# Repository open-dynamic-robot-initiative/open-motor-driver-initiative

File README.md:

# Software for the Open Motor Driver Initiative project - uOmodri board

## Required installs
In order to use the UOMODRI projects, you must install [Code Composer Studio (CCS)](https://software-dl.ti.com/ccs/esd/documents/ccs_downloads.html) and [C2000Ware library](https://www.ti.com/tool/C2000WARE#downloads) from Texas Instruments. C2000Ware Motor Control SDK is not necessary anymore. 
The [installation](https://software-dl.ti.com/ccs/esd/documents/users_guide/index_installation.html) procedure is available on TI website.
For Linux users, don't forget to install USB drivers (everything is explained on Texas Instrument website).
When installing CCS, prefer a custom installation and check "C2000 real-time MCUs" installation.

## Repository description
This repository contains one project:
	**uOmodri_c28** : Main project. Implements current, speed and position control for PMSM along with a SPI communication for commands or debug. 
3 Files are mainly used for configuration:
- inc\uomodri_user_defines.h : Saves all the defines used in the project.
- inc\uomodri_hal_config_handlers.h : Structures necessaries during initialization phase.
- inc\uomodri_prj_config_handlers.h : Structures used in the running phase of the project.

## How to import these project
After cloning the repository, you can import the projects by doing Project > Import CCS project.
The last thing you must do before being able to compile the projects is to define the path to your C2000Ware library.
To do so, right click on the  project, and then Properties > Resource > Linked Resources.
Now modify the C2000WARE_ROOT path to match your own C2000Ware library folder path.
The folder should be named something like "C2000Ware_4_01_00_00" for the 4.01.00.00 version.
Verify that PARENT_LOC and WORKSPACE_LOC point on your own working workspace.

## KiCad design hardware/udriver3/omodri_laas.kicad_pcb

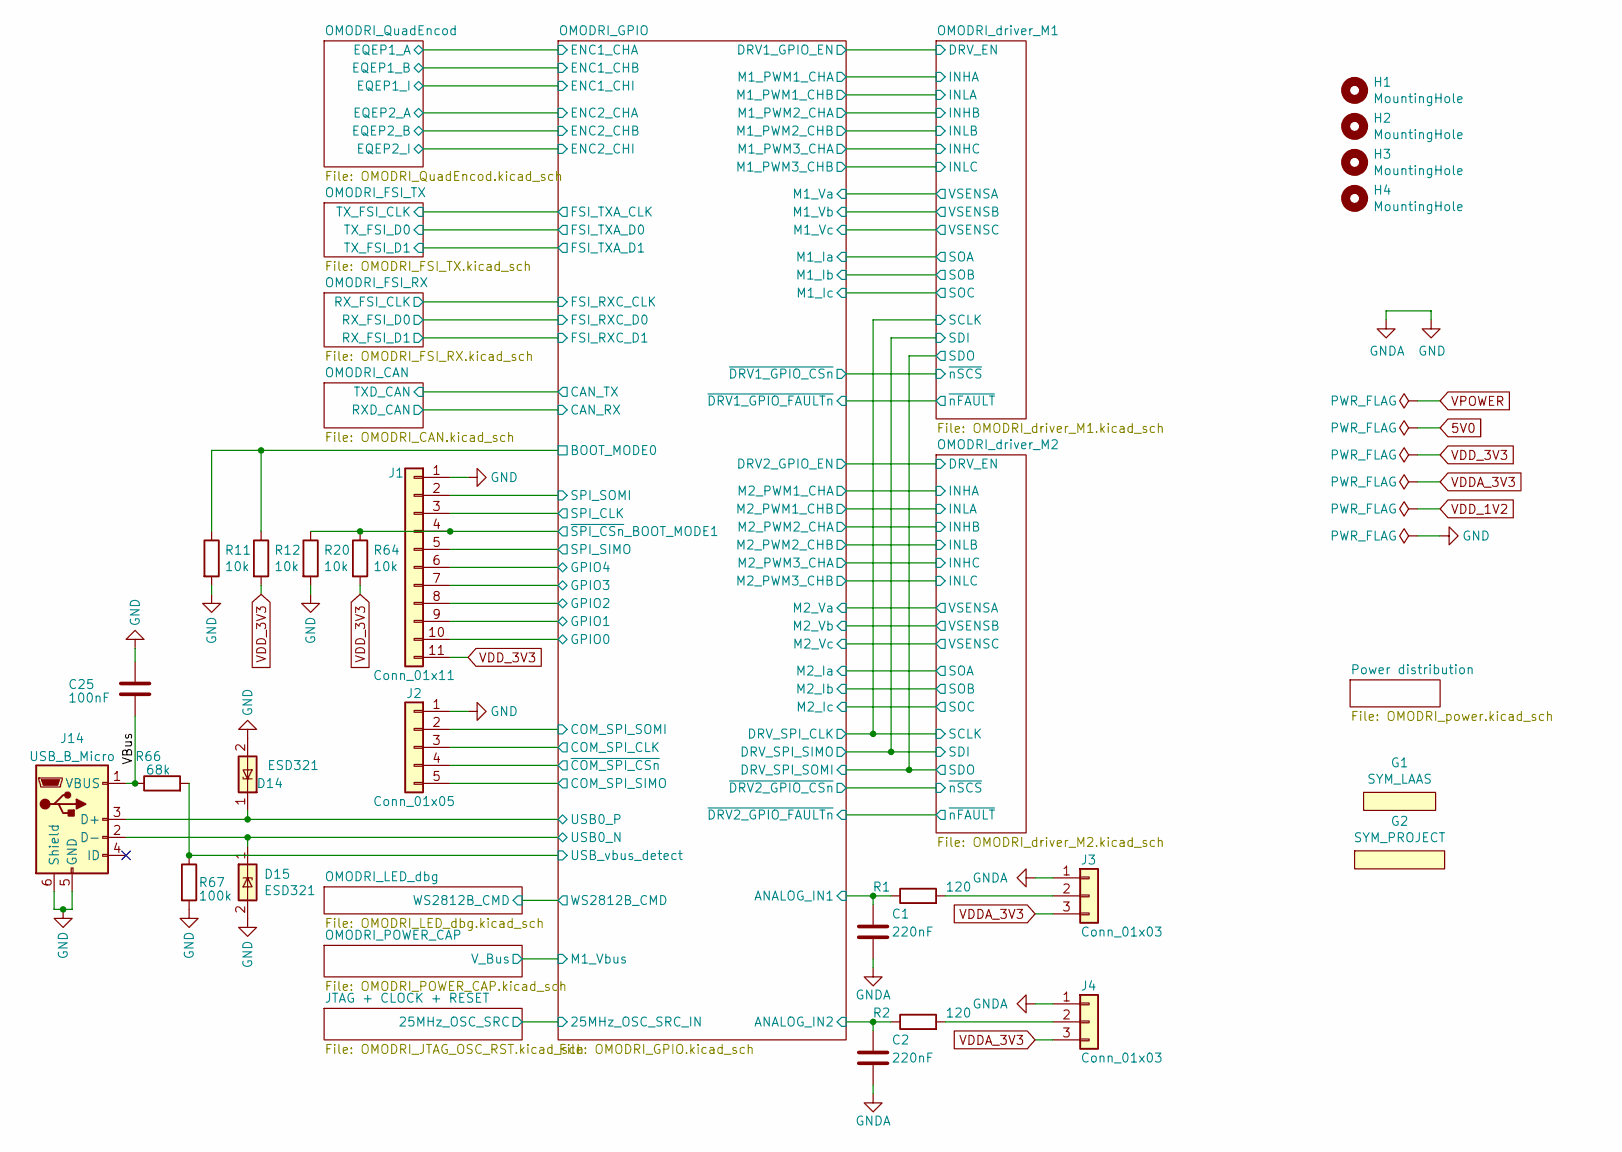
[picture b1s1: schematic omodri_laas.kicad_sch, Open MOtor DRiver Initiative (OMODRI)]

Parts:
C1, C2: 220nF; C_0201_0603Metric; Rated Voltage 25V; Part No GRM033R61C224KE14D; DigiKey 490-17040-1-ND
C25: 100nF; C_0201_0603Metric; Rated Voltage 10V; Part No GRM033R61E104KE14J; Farnell 3790414
D14, D15: ESD321; D_0402_1005Metric; Part No ESD321DPYR; DigiKey 296-51108-1-ND
G1: SYM_LAAS; logo_laas
G2: SYM_PROJECT; logo_OpenHardware
H1, H2, H3, H4: MountingHole; MountingHole_2.2mm_M2
J1: Conn_01x11; Hirose_DF13-11P-1.25DSA_1x11_P1.25mm_Vertical; Part No DF13-11P-1.25DSA; DigiKey DF13-11P-1.25DSA-ND
J2: Conn_01x05; Hirose_DF13-05P-1.25DSA_1x05_P1.25mm_Vertical; Part No DF13-5P-1.25DSA; DigiKey H2194-ND
J3, J4: Conn_01x03; Hirose_DF13-03P-1.25DSA_1x03_P1.25mm_Vertical; Part No DF13-3P-1.25DSA; DigiKey H2192-ND
J14: USB_B_Micro; USB_Micro-B_Molex_47346-0001; Part No 473460001; DigiKey WM17141CT-ND
R1, R2: 120; R_0201_0603Metric; Part No ERJ-1GNF1200C; DigiKey P122692CT-ND
R11, R12, R20, R64: 10k; R_0201_0603Metric; Part No ERJ-1GNF1002C; DigiKey P122414CT-ND
R66: 68k; R_0201_0603Metric; Part No ERJ1GNJ683C; DigiKey P123361CT-ND
R67: 100k; R_0201_0603Metric; Part No ERJ-1GNF1003C; DigiKey P122655CT-ND

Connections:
/OMODRI_GPIO/ANALOG_IN1: C1.1, R1.1; also elsewhere on the board
/OMODRI_GPIO/ANALOG_IN2: C2.1, R2.1; also elsewhere on the board
/OMODRI_GPIO/BOOT_MODE0: R11.1, R12.1; also elsewhere on the board
/OMODRI_GPIO/COM_SPI_CLK: J2.3; also elsewhere on the board
/OMODRI_GPIO/COM_SPI_SIMO: J2.5; also elsewhere on the board
/OMODRI_GPIO/COM_SPI_SOMI: J2.2; also elsewhere on the board
/OMODRI_GPIO/GPIO0: J1.10; also elsewhere on the board
/OMODRI_GPIO/GPIO1: J1.9; also elsewhere on the board
/OMODRI_GPIO/GPIO2: J1.8; also elsewhere on the board
/OMODRI_GPIO/GPIO3: J1.7; also elsewhere on the board
/OMODRI_GPIO/GPIO4: J1.6; also elsewhere on the board
/OMODRI_GPIO/SPI_CLK: J1.3; also elsewhere on the board
/OMODRI_GPIO/SPI_SIMO: J1.5; also elsewhere on the board
/OMODRI_GPIO/SPI_SOMI: J1.2; also elsewhere on the board
/OMODRI_GPIO/USB0_N: D15.1 (IO1), J14.2 (D-); also elsewhere on the board
/OMODRI_GPIO/USB0_P: D14.1 (IO1), J14.3 (D+); also elsewhere on the board
/OMODRI_GPIO/USB_vbus_detect: R66.2, R67.1; also elsewhere on the board
/OMODRI_GPIO/~COM_SPI_CSn~: J2.4; also elsewhere on the board
/OMODRI_GPIO/~SPI_CSn~_BOOT_MODE1: J1.4, R20.1, R64.1; also elsewhere on the board
/VBus: C25.2, J14.1 (VBUS), R66.1
unnamed: J3.2, R1.2
unnamed: J4.2, R2.2
VDDA_3V3: J3.3, J4.3; also elsewhere on the board
VDD_3V3: J1.11, R12.2, R64.2; also elsewhere on the board

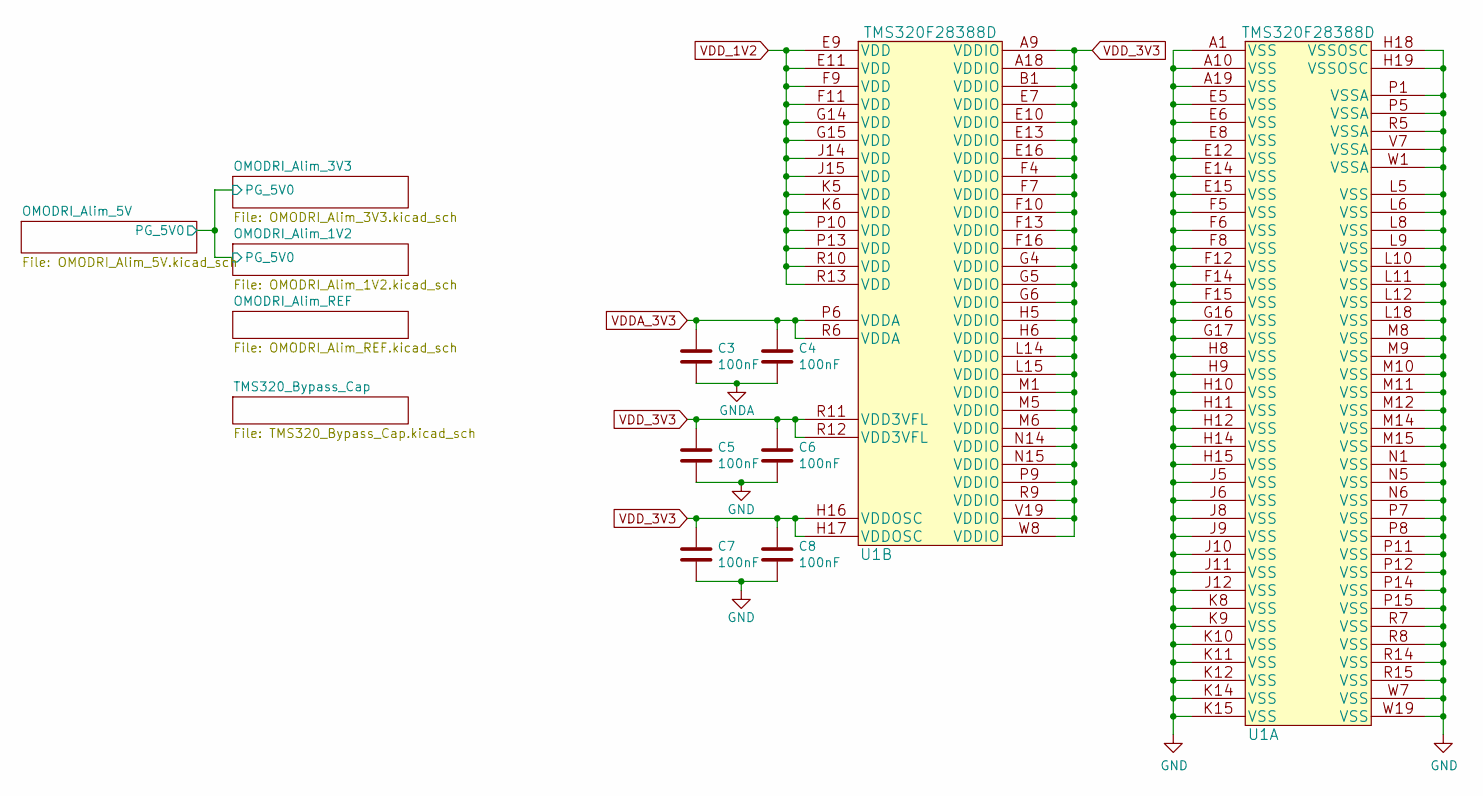
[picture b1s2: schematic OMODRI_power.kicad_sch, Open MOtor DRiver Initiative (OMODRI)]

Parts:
C3, C4, C5, C6, C7, C8: 100nF; C_0201_0603Metric; Rated Voltage 10V; Part No GRM033R61E104KE14J; Farnell 3790414
U1: TMS320F28388D; NFBGA_337; Part No F28388DZWTS; DigiKey 296-F28388DZWTS-ND

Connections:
VDDA_3V3: C3.1, C4.1, U1.P6 (VDDA), U1.R6 (VDDA); also elsewhere on the board
VDD_1V2: U1.E9 (VDD), U1.E11 (VDD), U1.F9 (VDD), U1.F11 (VDD), U1.G14 (VDD), U1.G15 (VDD), U1.J14 (VDD), U1.J15 (VDD), U1.K5 (VDD), U1.K6 (VDD), U1.P10 (VDD), U1.P13 (VDD), U1.R10 (VDD), U1.R13 (VDD); also elsewhere on the board
VDD_3V3: C5.1, C6.1, C7.1, C8.1, U1.A9 (VDDIO), U1.A18 (VDDIO), U1.B1 (VDDIO), U1.E7 (VDDIO), U1.E10 (VDDIO), U1.E13 (VDDIO), U1.E16 (VDDIO), U1.F4 (VDDIO), U1.F7 (VDDIO), U1.F10 (VDDIO), U1.F13 (VDDIO), U1.F16 (VDDIO), U1.G4 (VDDIO), U1.G5 (VDDIO), U1.G6 (VDDIO), U1.H5 (VDDIO), U1.H6 (VDDIO), U1.H16 (VDDOSC), U1.H17 (VDDOSC), U1.L14 (VDDIO), U1.L15 (VDDIO), U1.M1 (VDDIO), U1.M5 (VDDIO), U1.M6 (VDDIO), U1.N14 (VDDIO), U1.N15 (VDDIO), U1.P9 (VDDIO), U1.R9 (VDDIO), U1.R11 (VDD3VFL), U1.R12 (VDD3VFL), U1.V19 (VDDIO), U1.W8 (VDDIO); also elsewhere on the board

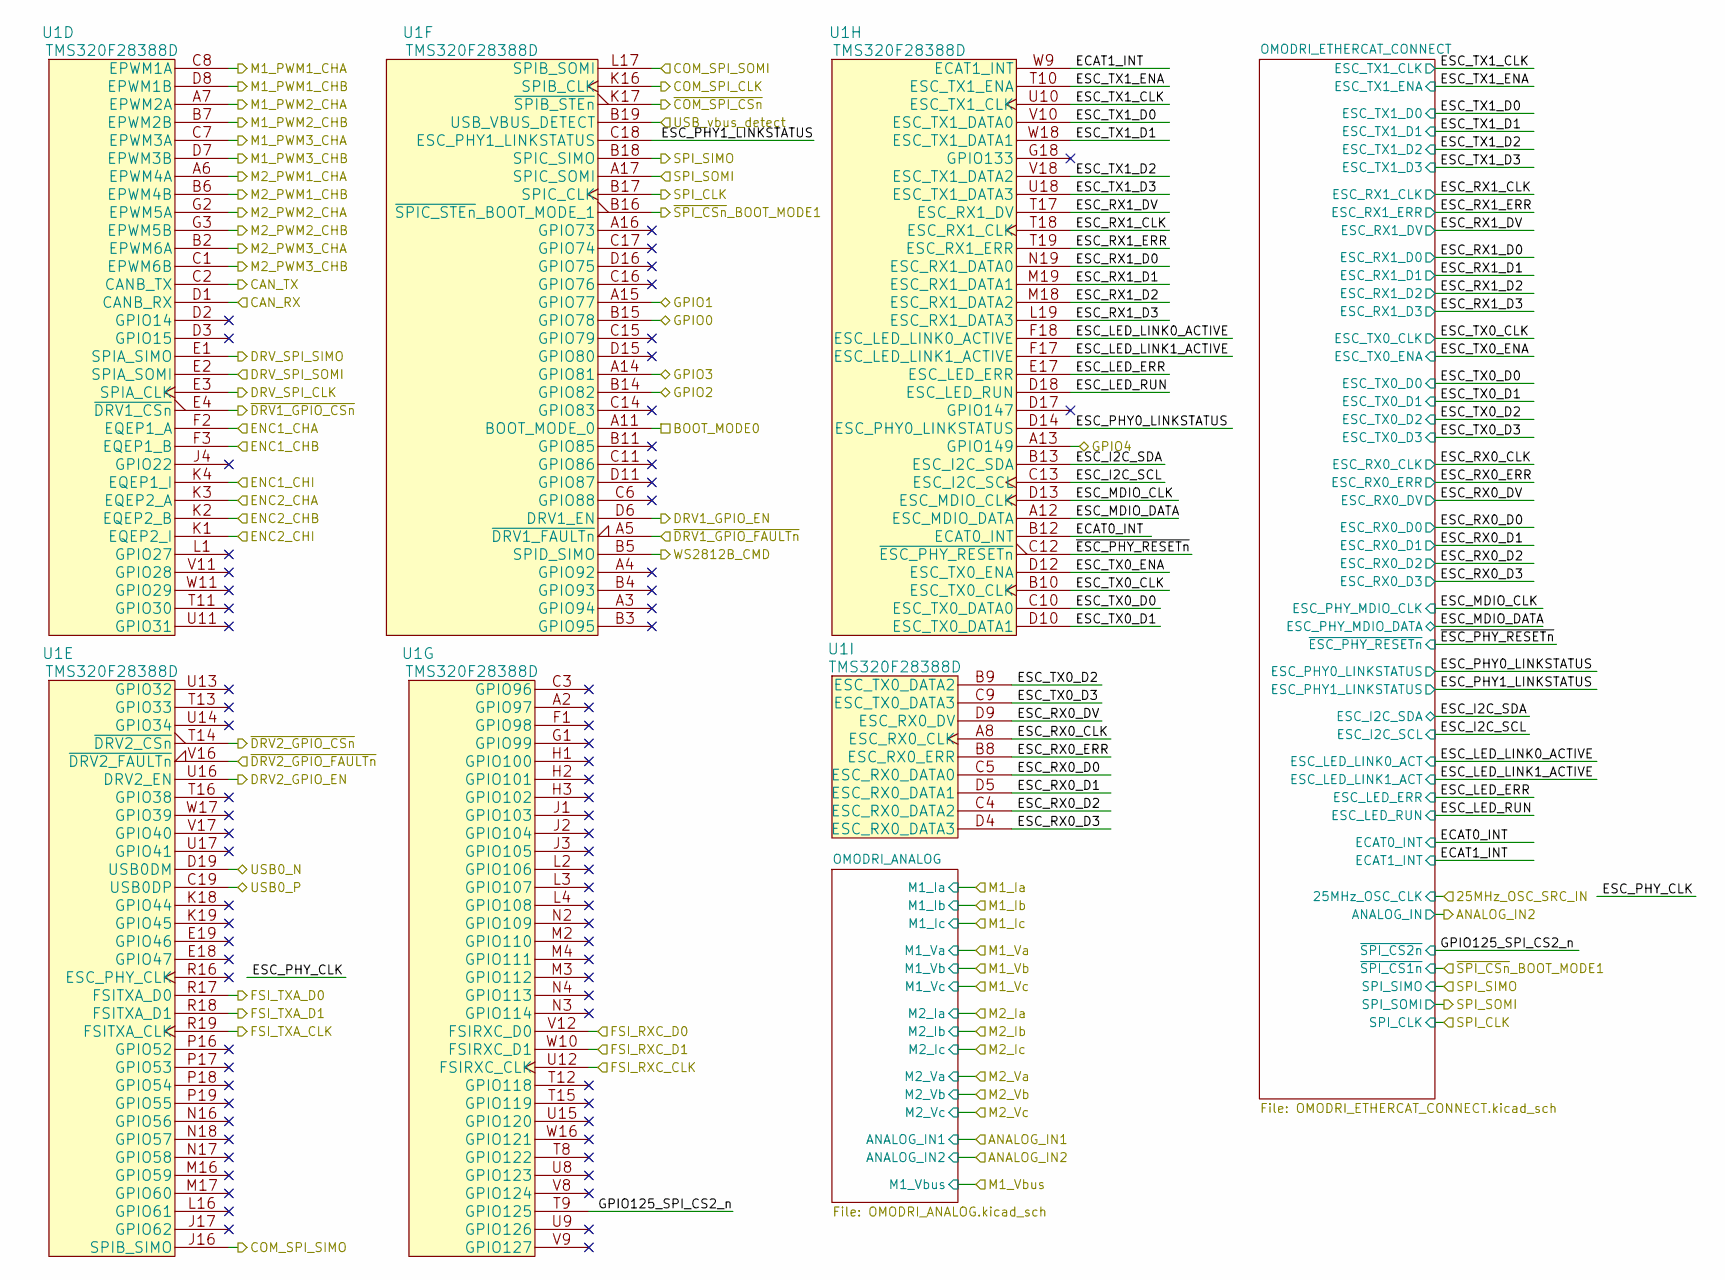
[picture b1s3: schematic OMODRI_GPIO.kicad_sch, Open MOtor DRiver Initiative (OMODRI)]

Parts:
U1: TMS320F28388D; NFBGA_337; Part No F28388DZWTS; DigiKey 296-F28388DZWTS-ND

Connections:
/OMODRI_GPIO/BOOT_MODE0: U1.A11 (BOOT_MODE_0); also elsewhere on the board
/OMODRI_GPIO/CAN_RX: U1.D1 (CANB_RX); also elsewhere on the board
/OMODRI_GPIO/CAN_TX: U1.C2 (CANB_TX); also elsewhere on the board
/OMODRI_GPIO/COM_SPI_CLK: U1.K16 (SPIB_CLK); also elsewhere on the board
/OMODRI_GPIO/COM_SPI_SIMO: U1.J16 (SPIB_SIMO); also elsewhere on the board
/OMODRI_GPIO/COM_SPI_SOMI: U1.L17 (SPIB_SOMI); also elsewhere on the board
/OMODRI_GPIO/DRV1_GPIO_EN: U1.D6 (DRV1_EN); also elsewhere on the board
/OMODRI_GPIO/DRV2_GPIO_EN: U1.U16 (DRV2_EN); also elsewhere on the board
/OMODRI_GPIO/DRV_SPI_CLK: U1.E3 (SPIA_CLK); also elsewhere on the board
/OMODRI_GPIO/DRV_SPI_SIMO: U1.E1 (SPIA_SIMO); also elsewhere on the board
/OMODRI_GPIO/DRV_SPI_SOMI: U1.E2 (SPIA_SOMI); also elsewhere on the board
/OMODRI_GPIO/ECAT0_INT: U1.B12 (ECAT0_INT); also elsewhere on the board
/OMODRI_GPIO/ECAT1_INT: U1.W9 (ECAT1_INT); also elsewhere on the board
/OMODRI_GPIO/ENC1_CHA: U1.F2 (EQEP1_A); also elsewhere on the board
/OMODRI_GPIO/ENC1_CHB: U1.F3 (EQEP1_B); also elsewhere on the board
/OMODRI_GPIO/ENC1_CHI: U1.K4 (EQEP1_I); also elsewhere on the board
/OMODRI_GPIO/ENC2_CHA: U1.K3 (EQEP2_A); also elsewhere on the board
/OMODRI_GPIO/ENC2_CHB: U1.K2 (EQEP2_B); also elsewhere on the board
/OMODRI_GPIO/ENC2_CHI: U1.K1 (EQEP2_I); also elsewhere on the board
/OMODRI_GPIO/ESC_I2C_SCL: U1.C13 (ESC_I2C_SCL); also elsewhere on the board
/OMODRI_GPIO/ESC_I2C_SDA: U1.B13 (ESC_I2C_SDA); also elsewhere on the board
/OMODRI_GPIO/ESC_LED_ERR: U1.E17 (ESC_LED_ERR); also elsewhere on the board
/OMODRI_GPIO/ESC_LED_LINK0_ACTIVE: U1.F18 (ESC_LED_LINK0_ACTIVE); also elsewhere on the board
/OMODRI_GPIO/ESC_LED_LINK1_ACTIVE: U1.F17 (ESC_LED_LINK1_ACTIVE); also elsewhere on the board
/OMODRI_GPIO/ESC_LED_RUN: U1.D18 (ESC_LED_RUN); also elsewhere on the board
/OMODRI_GPIO/ESC_MDIO_CLK: U1.D13 (ESC_MDIO_CLK); also elsewhere on the board
/OMODRI_GPIO/ESC_MDIO_DATA: U1.A12 (ESC_MDIO_DATA); also elsewhere on the board
/OMODRI_GPIO/ESC_PHY0_LINKSTATUS: U1.D14 (ESC_PHY0_LINKSTATUS); also elsewhere on the board
/OMODRI_GPIO/ESC_PHY1_LINKSTATUS: U1.C18 (ESC_PHY1_LINKSTATUS); also elsewhere on the board
/OMODRI_GPIO/ESC_RX0_CLK: U1.A8 (ESC_RX0_CLK); also elsewhere on the board
/OMODRI_GPIO/ESC_RX0_D0: U1.C5 (ESC_RX0_DATA0); also elsewhere on the board
/OMODRI_GPIO/ESC_RX0_D1: U1.D5 (ESC_RX0_DATA1); also elsewhere on the board
/OMODRI_GPIO/ESC_RX0_D2: U1.C4 (ESC_RX0_DATA2); also elsewhere on the board
/OMODRI_GPIO/ESC_RX0_D3: U1.D4 (ESC_RX0_DATA3); also elsewhere on the board
/OMODRI_GPIO/ESC_RX0_DV: U1.D9 (ESC_RX0_DV); also elsewhere on the board
/OMODRI_GPIO/ESC_RX0_ERR: U1.B8 (ESC_RX0_ERR); also elsewhere on the board
/OMODRI_GPIO/ESC_RX1_CLK: U1.T18 (ESC_RX1_CLK); also elsewhere on the board
/OMODRI_GPIO/ESC_RX1_D0: U1.N19 (ESC_RX1_DATA0); also elsewhere on the board
/OMODRI_GPIO/ESC_RX1_D1: U1.M19 (ESC_RX1_DATA1); also elsewhere on the board
/OMODRI_GPIO/ESC_RX1_D2: U1.M18 (ESC_RX1_DATA2); also elsewhere on the board
/OMODRI_GPIO/ESC_RX1_D3: U1.L19 (ESC_RX1_DATA3); also elsewhere on the board
/OMODRI_GPIO/ESC_RX1_DV: U1.T17 (ESC_RX1_DV); also elsewhere on the board
/OMODRI_GPIO/ESC_RX1_ERR: U1.T19 (ESC_RX1_ERR); also elsewhere on the board
/OMODRI_GPIO/ESC_TX0_CLK: U1.B10 (ESC_TX0_CLK); also elsewhere on the board
/OMODRI_GPIO/ESC_TX0_D0: U1.C10 (ESC_TX0_DATA0); also elsewhere on the board
/OMODRI_GPIO/ESC_TX0_D1: U1.D10 (ESC_TX0_DATA1); also elsewhere on the board
/OMODRI_GPIO/ESC_TX0_D2: U1.B9 (ESC_TX0_DATA2); also elsewhere on the board
/OMODRI_GPIO/ESC_TX0_D3: U1.C9 (ESC_TX0_DATA3); also elsewhere on the board
/OMODRI_GPIO/ESC_TX0_ENA: U1.D12 (ESC_TX0_ENA); also elsewhere on the board
/OMODRI_GPIO/ESC_TX1_CLK: U1.U10 (ESC_TX1_CLK); also elsewhere on the board
/OMODRI_GPIO/ESC_TX1_D0: U1.V10 (ESC_TX1_DATA0); also elsewhere on the board
/OMODRI_GPIO/ESC_TX1_D1: U1.W18 (ESC_TX1_DATA1); also elsewhere on the board
/OMODRI_GPIO/ESC_TX1_D2: U1.V18 (ESC_TX1_DATA2); also elsewhere on the board
/OMODRI_GPIO/ESC_TX1_D3: U1.U18 (ESC_TX1_DATA3); also elsewhere on the board
/OMODRI_GPIO/ESC_TX1_ENA: U1.T10 (ESC_TX1_ENA); also elsewhere on the board
/OMODRI_GPIO/FSI_RXC_CLK: U1.U12 (FSIRXC_CLK); also elsewhere on the board
/OMODRI_GPIO/FSI_RXC_D0: U1.V12 (FSIRXC_D0); also elsewhere on the board
/OMODRI_GPIO/FSI_RXC_D1: U1.W10 (FSIRXC_D1); also elsewhere on the board
/OMODRI_GPIO/FSI_TXA_CLK: U1.R19 (FSITXA_CLK); also elsewhere on the board
/OMODRI_GPIO/FSI_TXA_D0: U1.R17 (FSITXA_D0); also elsewhere on the board
/OMODRI_GPIO/FSI_TXA_D1: U1.R18 (FSITXA_D1); also elsewhere on the board
/OMODRI_GPIO/GPIO0: U1.B15 (GPIO78); also elsewhere on the board
/OMODRI_GPIO/GPIO1: U1.A15 (GPIO77); also elsewhere on the board
/OMODRI_GPIO/GPIO2: U1.B14 (GPIO82); also elsewhere on the board
/OMODRI_GPIO/GPIO3: U1.A14 (GPIO81); also elsewhere on the board
/OMODRI_GPIO/GPIO4: U1.A13 (GPIO149); also elsewhere on the board
/OMODRI_GPIO/GPIO125_SPI_CS2_n: U1.T9 (GPIO125); also elsewhere on the board
/OMODRI_GPIO/SPI_CLK: U1.B17 (SPIC_CLK); also elsewhere on the board
/OMODRI_GPIO/SPI_SIMO: U1.B18 (SPIC_SIMO); also elsewhere on the board
/OMODRI_GPIO/SPI_SOMI: U1.A17 (SPIC_SOMI); also elsewhere on the board
/OMODRI_GPIO/USB0_N: U1.D19 (USB0DM); also elsewhere on the board
/OMODRI_GPIO/USB0_P: U1.C19 (USB0DP); also elsewhere on the board
/OMODRI_GPIO/USB_vbus_detect: U1.B19 (USB_VBUS_DETECT); also elsewhere on the board
/OMODRI_GPIO/WS2812B_CMD: U1.B5 (SPID_SIMO); also elsewhere on the board
/OMODRI_GPIO/~COM_SPI_CSn~: U1.K17 (~SPIB_STEn); also elsewhere on the board
/OMODRI_GPIO/~DRV1_GPIO_CSn~: U1.E4 (~DRV1_CSn); also elsewhere on the board
/OMODRI_GPIO/~DRV1_GPIO_FAULTn~: U1.A5 (~DRV1_FAULTn); also elsewhere on the board
/OMODRI_GPIO/~DRV2_GPIO_CSn~: U1.T14 (~DRV2_CSn); also elsewhere on the board
/OMODRI_GPIO/~DRV2_GPIO_FAULTn~: U1.V16 (~DRV2_FAULTn); also elsewhere on the board
/OMODRI_GPIO/~ESC_PHY_RESETn~: U1.C12 (~ESC_PHY_RESETn); also elsewhere on the board
/OMODRI_GPIO/~SPI_CSn~_BOOT_MODE1: U1.B16 (~SPIC_STEn_BOOT_MODE_1); also elsewhere on the board
/OMODRI_driver_M1/INHA: U1.C8 (EPWM1A); also elsewhere on the board
/OMODRI_driver_M1/INHB: U1.A7 (EPWM2A); also elsewhere on the board
/OMODRI_driver_M1/INHC: U1.C7 (EPWM3A); also elsewhere on the board
/OMODRI_driver_M1/INLA: U1.D8 (EPWM1B); also elsewhere on the board
/OMODRI_driver_M1/INLB: U1.B7 (EPWM2B); also elsewhere on the board
/OMODRI_driver_M1/INLC: U1.D7 (EPWM3B); also elsewhere on the board
/OMODRI_driver_M2/INHA: U1.A6 (EPWM4A); also elsewhere on the board
/OMODRI_driver_M2/INHB: U1.G2 (EPWM5A); also elsewhere on the board
/OMODRI_driver_M2/INHC: U1.B2 (EPWM6A); also elsewhere on the board
/OMODRI_driver_M2/INLA: U1.B6 (EPWM4B); also elsewhere on the board
/OMODRI_driver_M2/INLB: U1.G3 (EPWM5B); also elsewhere on the board
/OMODRI_driver_M2/INLC: U1.C1 (EPWM6B); also elsewhere on the board

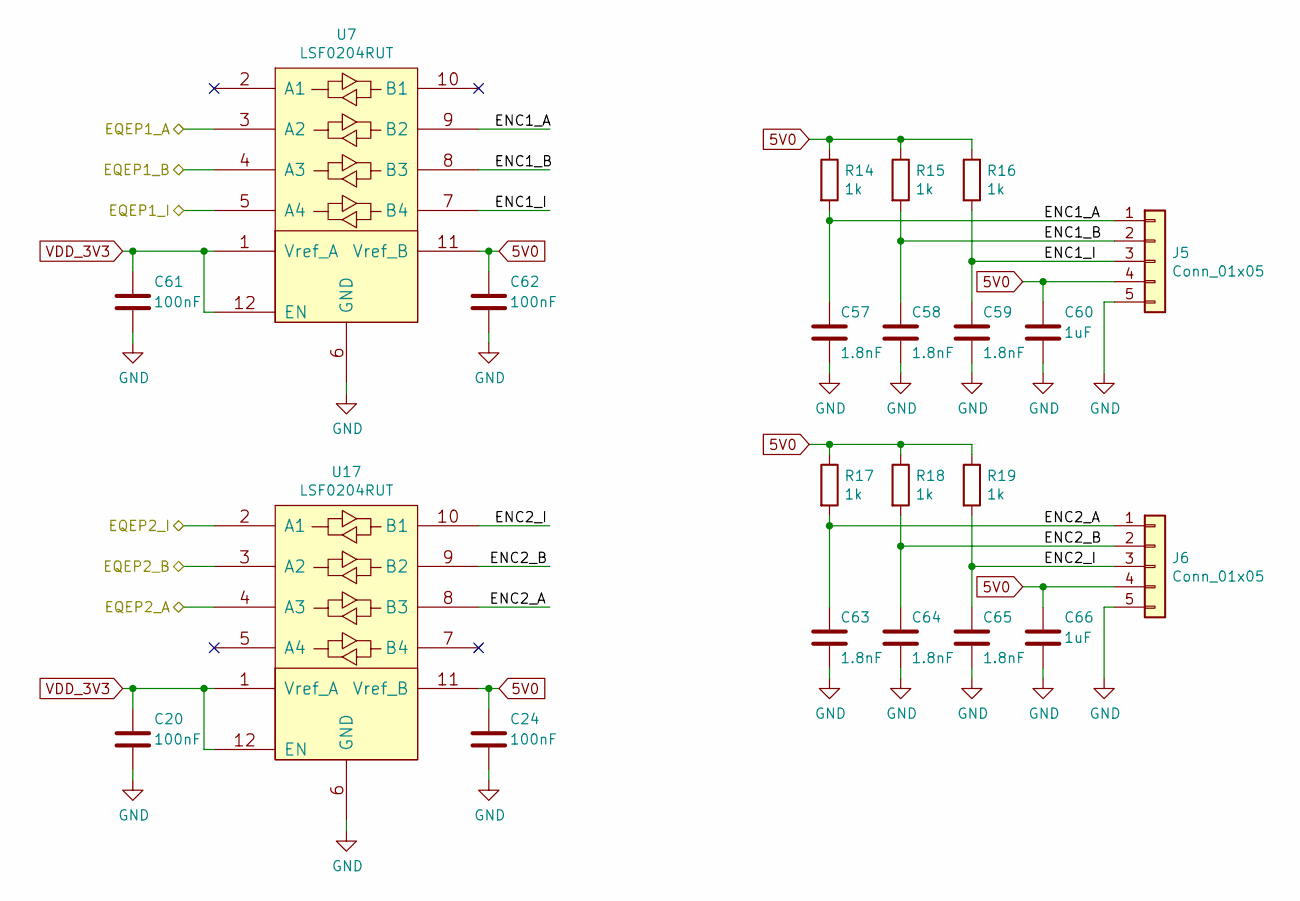
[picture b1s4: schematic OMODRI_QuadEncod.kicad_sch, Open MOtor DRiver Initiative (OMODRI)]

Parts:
C20, C24, C61, C62: 100nF; C_0201_0603Metric; Rated Voltage 10V; Part No GRM033R61E104KE14J; DigiKey 490-14571-1-ND
C57, C58, C59, C63, C64, C65: 1.8nF; C_0201_0603Metric; Rated Voltage 50V; Part No GRM033R71E182KA12D; DigiKey 490-GRM033R71E182KA12DTR-ND
C60, C66: 1uF; C_0201_0603Metric; Rated Voltage 10V; Part No GRM033C81A105ME05D; DigiKey 490-13219-1-ND
J5, J6: Conn_01x05; Hirose_DF13-05P-1.25DSA_1x05_P1.25mm_Vertical; Part No DF13-5P-1.25DSA; DigiKey H2194-ND
R14, R15, R16, R17, R18, R19: 1k; R_0201_0603Metric; Part No ERJ-1GNF1001C; DigiKey P122413CT-ND
U7, U17: LSF0204RUT; Texas_R_PUQFN-N12; Part No LSF0204RUTR; DigiKey 296-40404-1-ND

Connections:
/OMODRI_GPIO/ENC1_CHA: U7.3 (A2); also elsewhere on the board
/OMODRI_GPIO/ENC1_CHB: U7.4 (A3); also elsewhere on the board
/OMODRI_GPIO/ENC1_CHI: U7.5 (A4); also elsewhere on the board
/OMODRI_GPIO/ENC2_CHA: U17.4 (A3); also elsewhere on the board
/OMODRI_GPIO/ENC2_CHB: U17.3 (A2); also elsewhere on the board
/OMODRI_GPIO/ENC2_CHI: U17.2 (A1); also elsewhere on the board
/OMODRI_QuadEncod/ENC1_A: C57.1, J5.1, R14.2, U7.9 (B2)
/OMODRI_QuadEncod/ENC1_B: C58.1, J5.2, R15.2, U7.8 (B3)
/OMODRI_QuadEncod/ENC1_I: C59.1, J5.3, R16.2, U7.7 (B4)
/OMODRI_QuadEncod/ENC2_A: C63.1, J6.1, R17.2, U17.8 (B3)
/OMODRI_QuadEncod/ENC2_B: C64.1, J6.2, R18.2, U17.9 (B2)
/OMODRI_QuadEncod/ENC2_I: C65.1, J6.3, R19.2, U17.10 (B1)
VDD_3V3: C20.1, C61.1, U7.1 (Vref_A), U7.12 (EN), U17.1 (Vref_A), U17.12 (EN); also elsewhere on the board

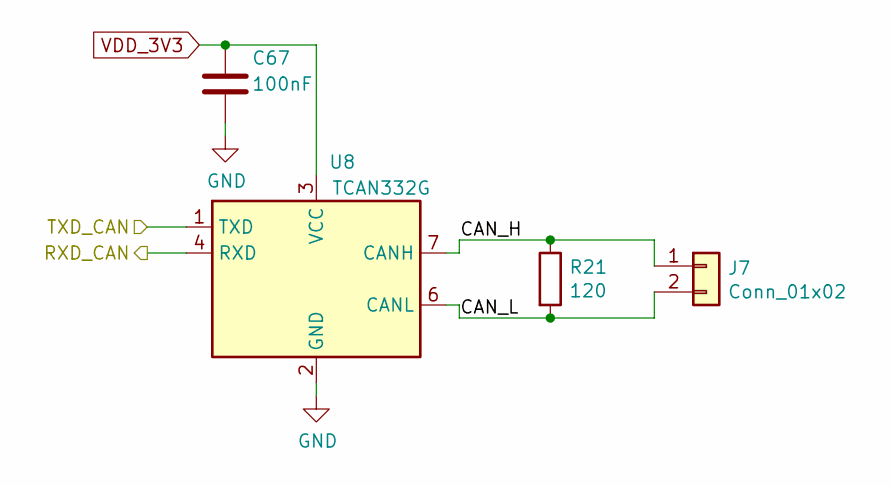
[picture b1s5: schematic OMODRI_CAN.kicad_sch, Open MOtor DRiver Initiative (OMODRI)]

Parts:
C67: 100nF; C_0201_0603Metric; Rated Voltage 10V; Part No GRM033R61E104KE14J; DigiKey 490-14571-1-ND
J7: Conn_01x02; Hirose_DF13-02P-1.25DSA_1x02_P1.25mm_Vertical; Part No DF13-2P-1.25DSA; DigiKey H2191-ND
R21: 120; R_0201_0603Metric; Part No ERJ-1GNF1200C; DigiKey P122692CT-ND
U8: TCAN332G; TSOT-23-8; Part No TCAN332GDCNR; DigiKey 296-48677-1-ND

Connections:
/OMODRI_CAN/CAN_H: J7.1, R21.1, U8.7 (CANH)
/OMODRI_CAN/CAN_L: J7.2, R21.2, U8.6 (CANL)
/OMODRI_GPIO/CAN_RX: U8.4 (RXD); also elsewhere on the board
/OMODRI_GPIO/CAN_TX: U8.1 (TXD); also elsewhere on the board
VDD_3V3: C67.1, U8.3 (VCC); also elsewhere on the board

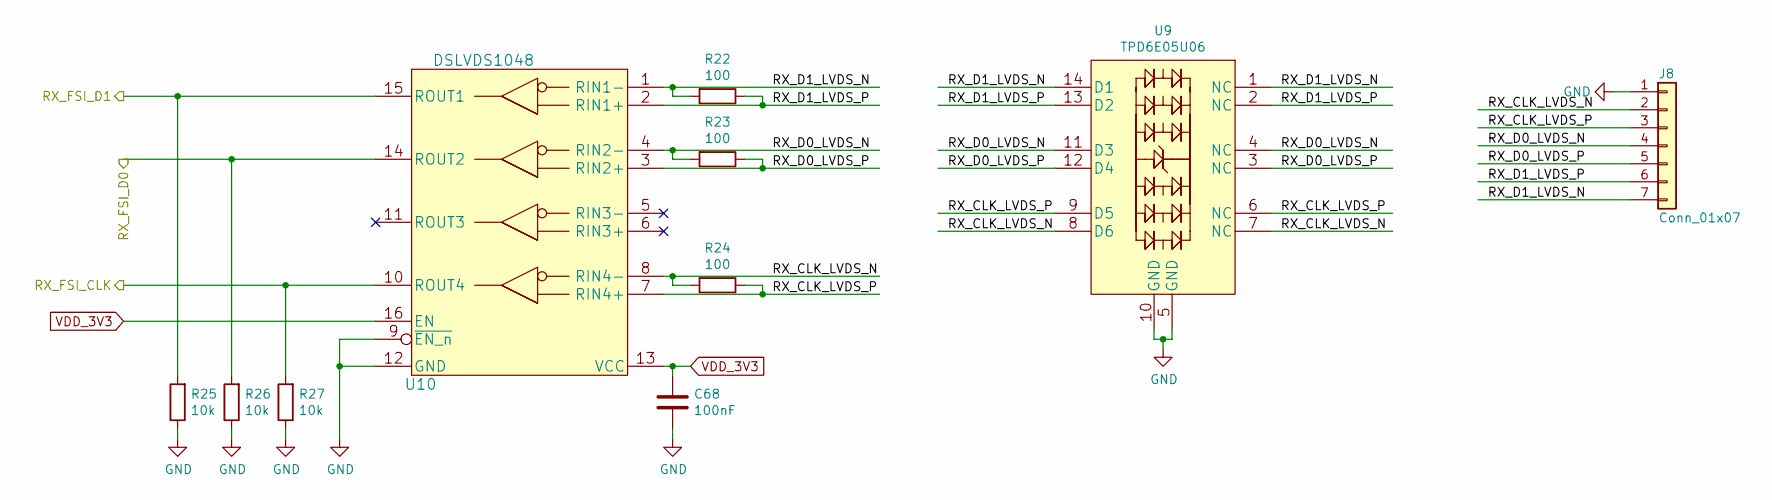
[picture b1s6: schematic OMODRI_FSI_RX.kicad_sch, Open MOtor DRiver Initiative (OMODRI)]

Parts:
C68: 100nF; C_0201_0603Metric; Rated Voltage 10V; Part No GRM033R61E104KE14J; Farnell 3790414
J8: Conn_01x07; Hirose_DF13-07P-1.25DSA_1x07_P1.25mm_Vertical; Part No DF13-7P-1.25DSA; DigiKey H2196-ND
R22, R23, R24: 100; R_0201_0603Metric; Part No ERJ-1GNF1000C; DigiKey P122654CT-ND
R25, R26, R27: 10k; R_0201_0603Metric; Part No ERJ-1GNF1002C; DigiKey P122414CT-ND
U9: TPD6E05U06; USON_14; Part No TPD6E05U06RVZR; DigiKey 296-39349-1-ND
U10: DSLVDS1048; TSSOP-16_4.4x5mm_P0.65mm; Part No DSLVDS1048PWR; DigiKey 296-51106-1-ND

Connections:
/OMODRI_FSI_RX/RX_CLK_LVDS_N: J8.2, R24.2, U9.7 (NC), U9.8 (D6), U10.8 (RIN4-)
/OMODRI_FSI_RX/RX_CLK_LVDS_P: J8.3, R24.1, U9.6 (NC), U9.9 (D5), U10.7 (RIN4+)
/OMODRI_FSI_RX/RX_D0_LVDS_N: J8.4, R23.2, U9.4 (NC), U9.11 (D3), U10.4 (RIN2-)
/OMODRI_FSI_RX/RX_D0_LVDS_P: J8.5, R23.1, U9.3 (NC), U9.12 (D4), U10.3 (RIN2+)
/OMODRI_FSI_RX/RX_D1_LVDS_N: J8.7, R22.2, U9.1 (NC), U9.14 (D1), U10.1 (RIN1-)
/OMODRI_FSI_RX/RX_D1_LVDS_P: J8.6, R22.1, U9.2 (NC), U9.13 (D2), U10.2 (RIN1+)
/OMODRI_GPIO/FSI_RXC_CLK: R27.2, U10.10 (ROUT4); also elsewhere on the board
/OMODRI_GPIO/FSI_RXC_D0: R26.2, U10.14 (ROUT2); also elsewhere on the board
/OMODRI_GPIO/FSI_RXC_D1: R25.2, U10.15 (ROUT1); also elsewhere on the board
VDD_3V3: C68.1, U10.13 (VCC), U10.16 (EN); also elsewhere on the board

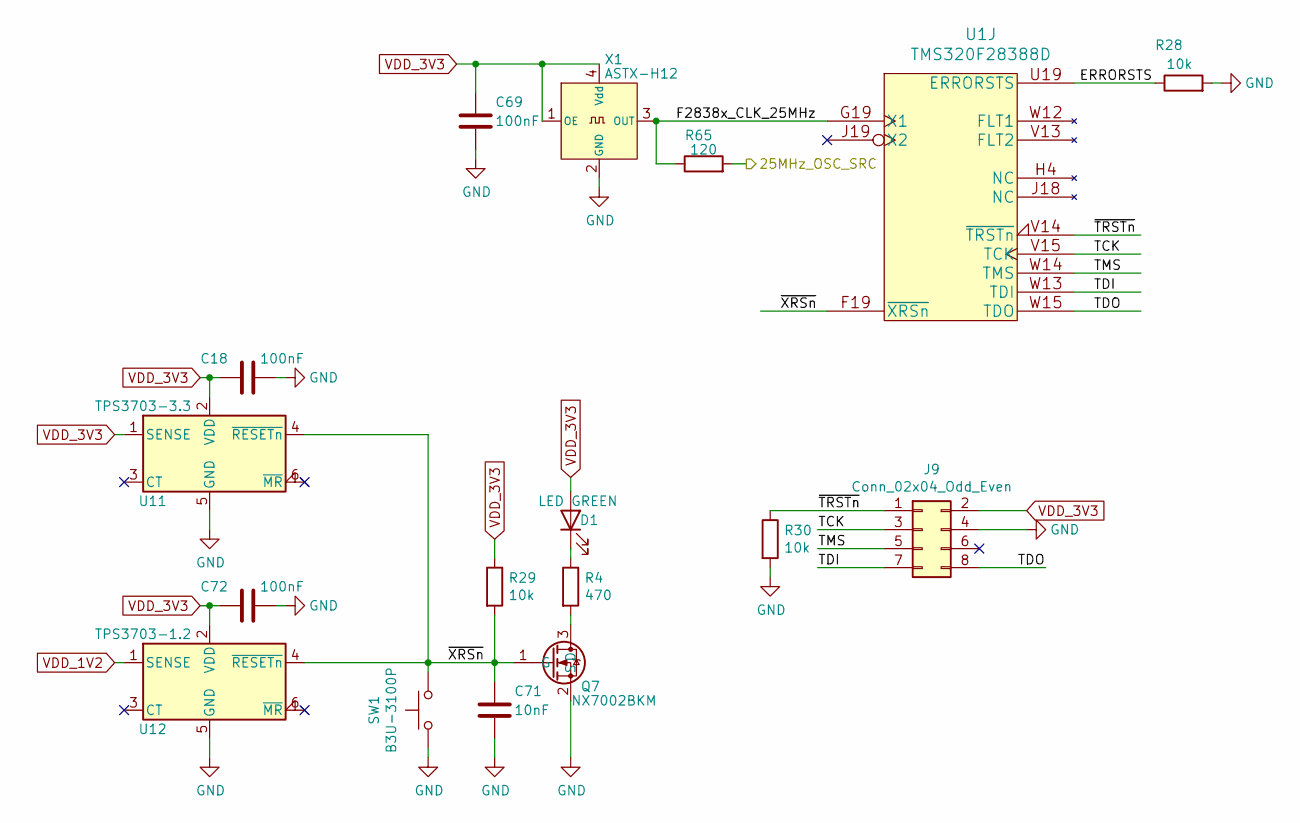
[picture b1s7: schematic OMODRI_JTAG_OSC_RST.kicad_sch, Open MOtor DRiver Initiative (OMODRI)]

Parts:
C18, C72: 100nF; C_0201_0603Metric; Rated Voltage 10V; Part No GRM033R61E104KE14J; Farnell 3790414
C69: 100nF; C_0201_0603Metric; Rated Voltage 10V; Part No GRM033R61E104KE14J; DigiKey 490-14571-1-ND
C71: 10nF; C_0201_0603Metric; Rated Voltage 25V; Part No GRM033R71E103KE14D; DigiKey 490-14454-1-ND
D1: LED GREEN; LED_0402_1005Metric; Part No HSMG-C280; DigiKey 516-3066-1-ND
J9: Conn_02x04_Odd_Even; PinSocket_2x04_P1.27mm_Vertical; Part No 20021311-00008T4LF; DigiKey 609-3753-ND
Q7: NX7002BKM; Diodes_DFN1006-3; Part No NX7002BKMYL; DigiKey 1727-2232-1-ND
R4: 470; R_0201_0603Metric; Part No ERJ-1GNF4701C; DigiKey P123031CT-ND
R28, R29, R30: 10k; R_0201_0603Metric; Part No ERJ-1GNF1002C; DigiKey P122414CT-ND
R65: 120; R_0201_0603Metric; Part No ERJ-1GNF1200C; DigiKey P122692CT-ND
SW1: B3U-3100P; SW_SPST_B3U-1000P; Part No B3U-1000P; DigiKey SW1020CT-ND
U1: TMS320F28388D; NFBGA_337; Part No F28388DZWTS; DigiKey 296-F28388DZWTS-ND
U11: TPS3703-3.3; WSON-6_1.5x1.5mm_P0.5mm; Part No TPS3703A7330DSERQ1; DigiKey 296-TPS3703A7330DSERQ1CT-ND
U12: TPS3703-1.2; WSON-6_1.5x1.5mm_P0.5mm; Part No TPS3703A7120DSERQ1; DigiKey 296-TPS3703A7120DSERQ1CT-ND
X1: ASTX-H12; TCXO_SMD_Abracon_ASTX-H12-4Pin_2.5x2.0mm; Part No ASTX-H12-25.000MHZ-T; DigiKey 535-12041-1-ND

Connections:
/JTAG + CLOCK + RESET/25MHz_OSC_SRC: R65.2; also elsewhere on the board
/JTAG + CLOCK + RESET/ERRORSTS: R28.1, U1.U19 (ERRORSTS)
/JTAG + CLOCK + RESET/F2838x_CLK_25MHz: R65.1, U1.G19 (X1), X1.3 (OUT)
/JTAG + CLOCK + RESET/TCK: J9.3, U1.V15 (TCK)
/JTAG + CLOCK + RESET/TDI: J9.7, U1.W13 (TDI)
/JTAG + CLOCK + RESET/TDO: J9.8, U1.W15 (TDO)
/JTAG + CLOCK + RESET/TMS: J9.5, U1.W14 (TMS)
/JTAG + CLOCK + RESET/~TRSTn~: J9.1, R30.1, U1.V14 (~TRSTn)
/JTAG + CLOCK + RESET/~XRSn~: C71.1, Q7.1 (G), R29.2, SW1.2, U1.F19 (~XRSn), U11.4 (~RESETn), U12.4 (~RESETn)
unnamed: D1.1 (K), R4.1
unnamed: Q7.3 (D), R4.2
VDD_1V2: U12.1 (SENSE); also elsewhere on the board
VDD_3V3: C18.1, C69.1, C72.1, D1.2 (A), J9.2, R29.1, U11.1 (SENSE), U11.2 (VDD), U12.2 (VDD), X1.1 (OE), X1.4 (Vdd); also elsewhere on the board

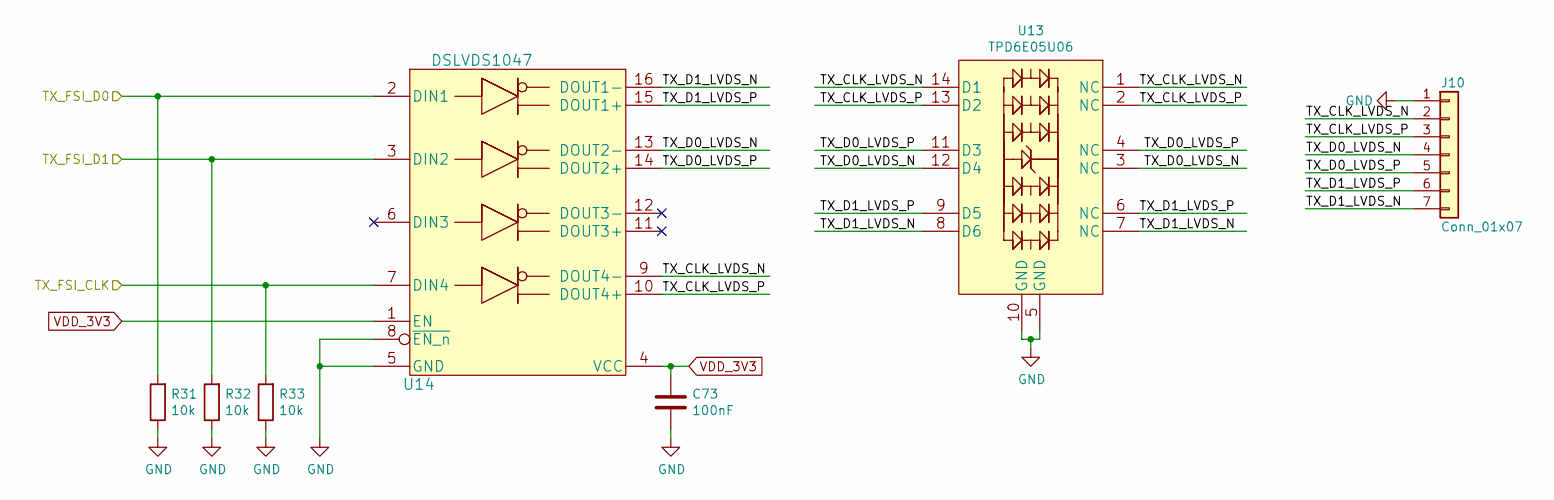
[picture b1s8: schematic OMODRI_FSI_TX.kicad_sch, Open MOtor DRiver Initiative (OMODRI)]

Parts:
C73: 100nF; C_0201_0603Metric; Rated Voltage 10V; Part No GRM033R61E104KE14J; Farnell 3790414
J10: Conn_01x07; Hirose_DF13-07P-1.25DSA_1x07_P1.25mm_Vertical; Part No DF13-7P-1.25DSA; DigiKey H2196-ND
R31, R32, R33: 10k; R_0201_0603Metric; Part No ERJ-1GNF1002C; DigiKey P122414CT-ND
U13: TPD6E05U06; USON_14; Part No TPD6E05U06RVZR; DigiKey 296-39349-1-ND
U14: DSLVDS1047; TSSOP-16_4.4x5mm_P0.65mm; Part No DSLVDS1047PWR; DigiKey 296-50740-1-ND

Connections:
/OMODRI_FSI_TX/TX_CLK_LVDS_N: J10.2, U13.1 (NC), U13.14 (D1), U14.9 (DOUT4-)
/OMODRI_FSI_TX/TX_CLK_LVDS_P: J10.3, U13.2 (NC), U13.13 (D2), U14.10 (DOUT4+)
/OMODRI_FSI_TX/TX_D0_LVDS_N: J10.4, U13.3 (NC), U13.12 (D4), U14.13 (DOUT2-)
/OMODRI_FSI_TX/TX_D0_LVDS_P: J10.5, U13.4 (NC), U13.11 (D3), U14.14 (DOUT2+)
/OMODRI_FSI_TX/TX_D1_LVDS_N: J10.7, U13.7 (NC), U13.8 (D6), U14.16 (DOUT1-)
/OMODRI_FSI_TX/TX_D1_LVDS_P: J10.6, U13.6 (NC), U13.9 (D5), U14.15 (DOUT1+)
/OMODRI_GPIO/FSI_TXA_CLK: R33.2, U14.7 (DIN4); also elsewhere on the board
/OMODRI_GPIO/FSI_TXA_D0: R31.2, U14.2 (DIN1); also elsewhere on the board
/OMODRI_GPIO/FSI_TXA_D1: R32.2, U14.3 (DIN2); also elsewhere on the board
VDD_3V3: C73.1, U14.1 (EN), U14.4 (VCC); also elsewhere on the board
